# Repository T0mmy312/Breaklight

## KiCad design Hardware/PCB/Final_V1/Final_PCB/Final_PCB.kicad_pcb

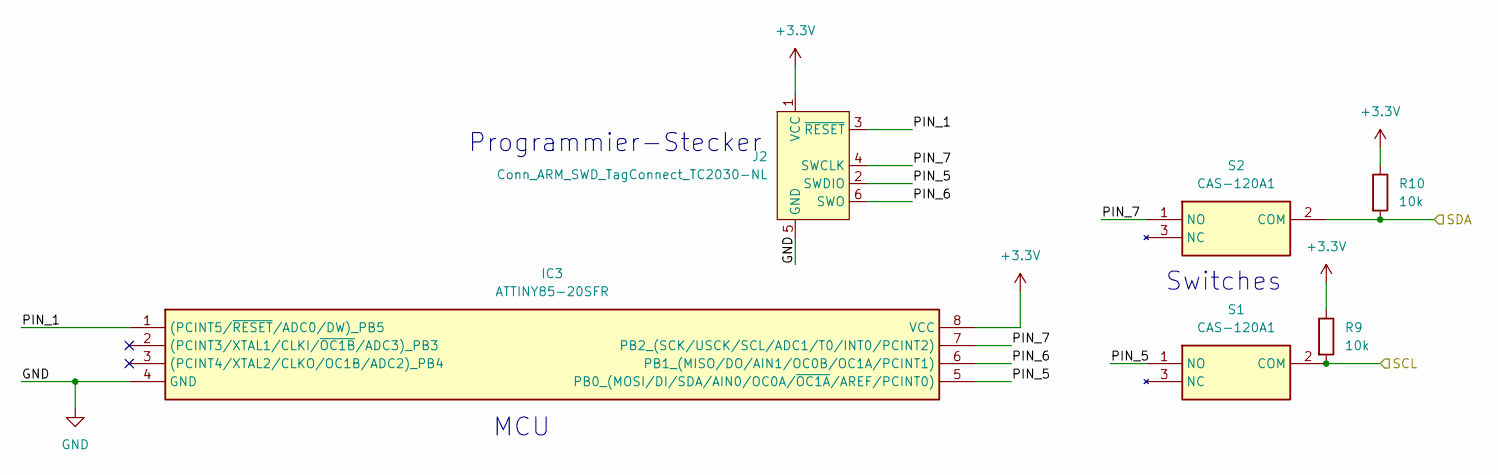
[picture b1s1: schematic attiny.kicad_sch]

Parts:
IC3: ATTINY85-20SFR; SOIC127P798X216-8N; Mouser Part Number 556-ATTINY85-20SFR
J2: Conn_ARM_SWD_TagConnect_TC2030-NL; Tag-Connect_TC2030-IDC-NL_2x03_P1.27mm_Vertical
R9, R10: 10k; R_0603_1608Metric
S1, S2: CAS-120A1; CAS120A1; Mouser Part Number 229-CAS-120A1

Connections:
+3.3V: IC3.8 (VCC), J2.1 (VCC), R9.1, R10.1; also elsewhere on the board
/ATTiny/PIN_1: IC3.1 ((PCINT5/~RESET/ADC0/DW)_PB5), J2.3 (~RESET)
/ATTiny/PIN_5: IC3.5 (PB0_(MOSI/DI/SDA/AIN0/OC0A/~OC1A/AREF/P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), J2.2 (SWDIO), S1.1 (NO)
/ATTiny/PIN_6: IC3.6 (PB1_(MISO/DO/AIN1/OC0B/OC1A/PCINT1)), J2.6 (SWO)
/ATTiny/PIN_7: IC3.7 (PB2_(SCK/USCK/SCL/ADC1/T0/INT0/PCINT2)), J2.4 (SWCLK), S2.1 (NO)
/ATTiny/SCL: R9.2, S1.2 (COM); also elsewhere on the board
/ATTiny/SDA: R10.2, S2.2 (COM); also elsewhere on the board
GND: IC3.4 (GND), J2.5 (GND); also elsewhere on the board

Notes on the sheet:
Switches
Programmier-Stecker
MCU

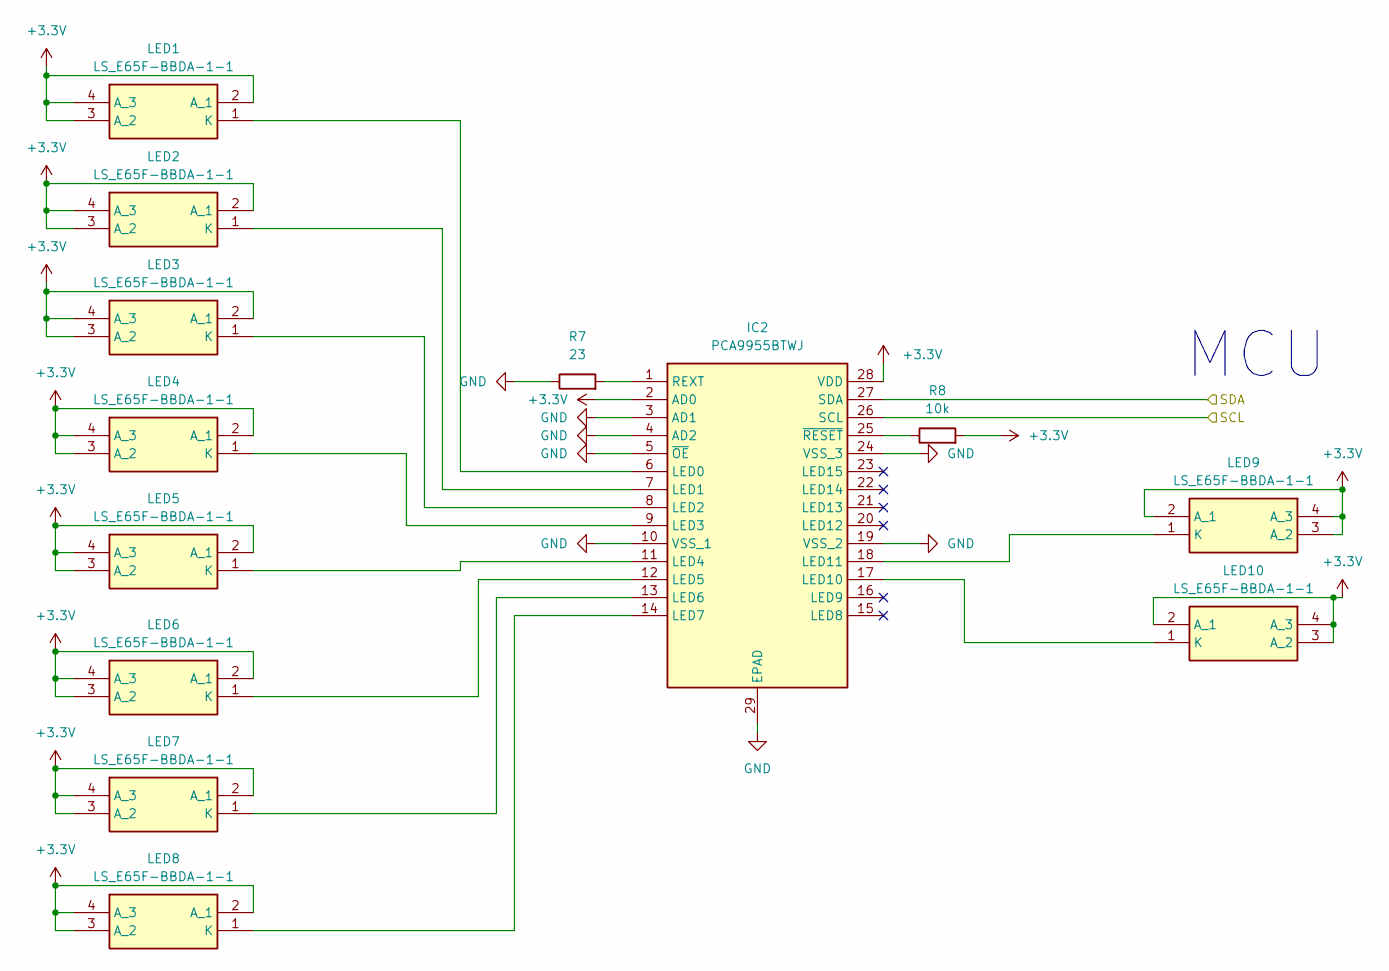
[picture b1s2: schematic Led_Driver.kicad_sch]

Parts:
IC2: PCA9955BTWJ; SOP65P640X110-29N; Manufacturer_Part_Number PCA9955BTWJ
LED1, LED2, LED3, LED4, LED5, LED6, LED7, LED8, LED9, LED10: LS_E65F-BBDA-1-1; LSE65FBBDA11; Mouser Part Number 720-LSE65F-BBDA-1-Z
R7: 23; R_0603_1608Metric
R8: 10k; R_0603_1608Metric

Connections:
+3.3V: IC2.2 (AD0), IC2.28 (VDD), LED1.2 (A_1), LED1.3 (A_2), LED1.4 (A_3), LED2.2 (A_1), LED2.3 (A_2), LED2.4 (A_3), LED3.2 (A_1), LED3.3 (A_2), LED3.4 (A_3), LED4.2 (A_1), LED4.3 (A_2), LED4.4 (A_3), LED5.2 (A_1), LED5.3 (A_2), LED5.4 (A_3), LED6.2 (A_1), LED6.3 (A_2), LED6.4 (A_3), LED7.2 (A_1), LED7.3 (A_2), LED7.4 (A_3), LED8.2 (A_1), LED8.3 (A_2), LED8.4 (A_3), LED9.2 (A_1), LED9.3 (A_2), LED9.4 (A_3), LED10.2 (A_1), LED10.3 (A_2), LED10.4 (A_3), R8.2; also elsewhere on the board
/ATTiny/SCL: IC2.26 (SCL); also elsewhere on the board
/ATTiny/SDA: IC2.27 (SDA); also elsewhere on the board
GND: IC2.3 (AD1), IC2.4 (AD2), IC2.5 (~OE), IC2.10 (VSS_1), IC2.19 (VSS_2), IC2.24 (VSS_3), IC2.29 (EPAD), R7.1; also elsewhere on the board
unnamed: IC2.6 (LED0), LED1.1 (K)
unnamed: IC2.7 (LED1), LED2.1 (K)
unnamed: IC2.8 (LED2), LED3.1 (K)
unnamed: IC2.9 (LED3), LED4.1 (K)
unnamed: IC2.11 (LED4), LED5.1 (K)
unnamed: IC2.12 (LED5), LED6.1 (K)
unnamed: IC2.13 (LED6), LED7.1 (K)
unnamed: IC2.14 (LED7), LED8.1 (K)
unnamed: IC2.17 (LED10), LED10.1 (K)
unnamed: IC2.18 (LED11), LED9.1 (K)
unnamed: IC2.1 (REXT), R7.2
unnamed: IC2.25 (~RESET), R8.1

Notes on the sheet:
MCU

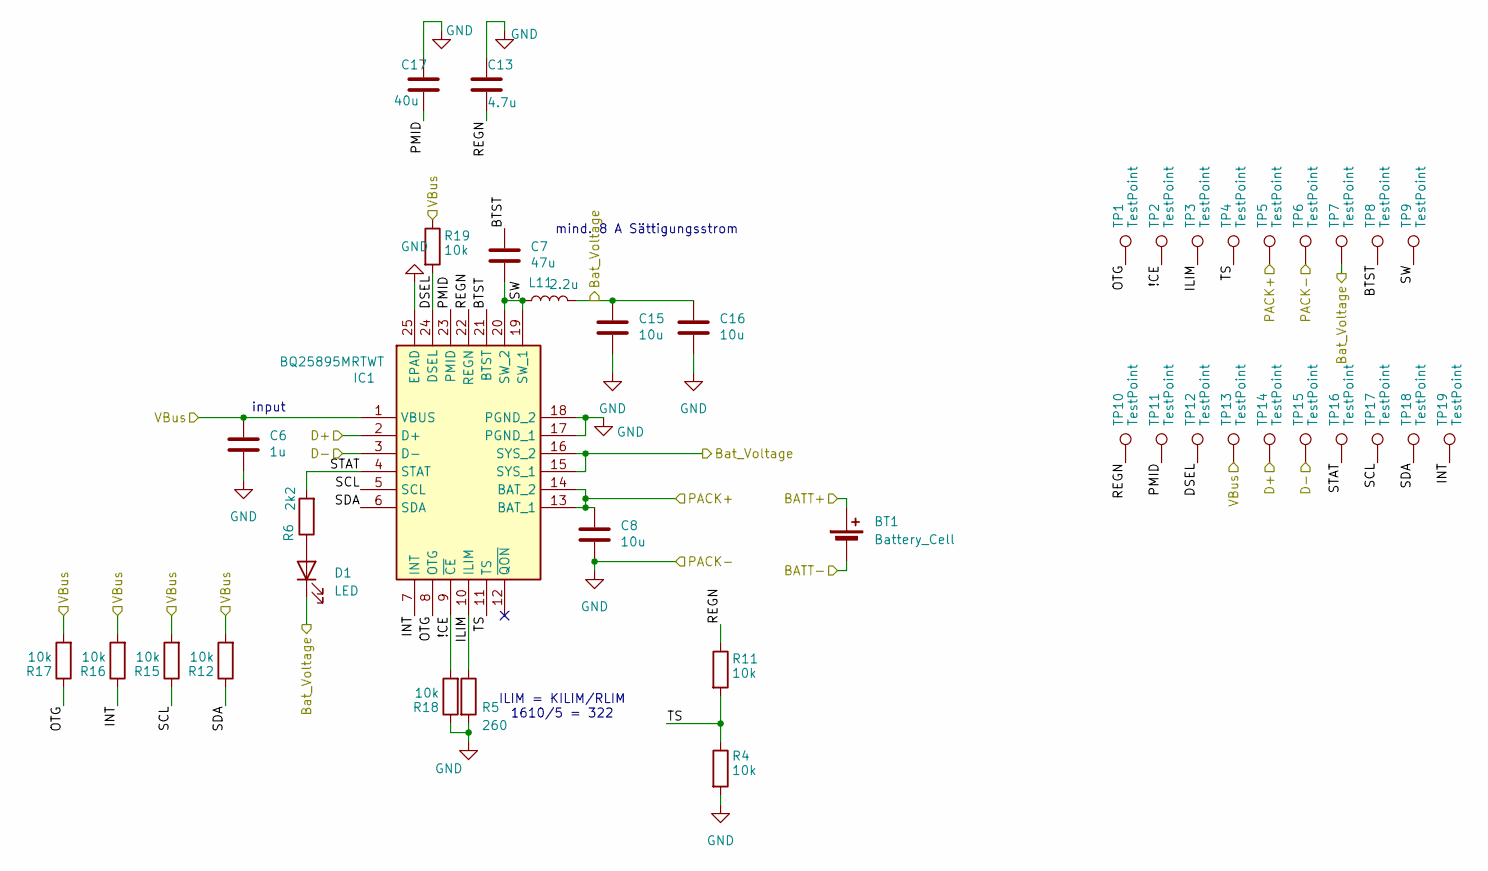
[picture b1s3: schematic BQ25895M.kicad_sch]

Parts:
BT1: Battery_Cell; PinHeader_1x02_P2.54mm_Vertical
C6: 1u; C_0603_1608Metric
C7: 47u; C_0603_1608Metric
C8, C15, C16: 10u; C_0603_1608Metric
C13: 4.7u; C_0603_1608Metric
C17: 40u; C_0603_1608Metric
D1: LED; LED_0603_1608Metric
IC1: BQ25895MRTWT; QFN50P400X400X80-25N-D; Mouser Part Number 595-BQ25895MRTWT
L11: 2.2u; L_0603_1608Metric
R4, R11, R12, R15, R16, R17, R18, R19: 10k; R_0603_1608Metric
R5: 260; R_0603_1608Metric
R6: 2k2; R_0603_1608Metric
TP1, TP2, TP3, TP4, TP5, TP6, TP7, TP8, TP9, TP10, TP11, TP12, TP13, TP14, TP15, TP16, TP17, TP18, TP19: TestPoint; TestPoint_Pad_1.5x1.5mm

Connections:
/BMS/BATT+: BT1.1 (+); also elsewhere on the board
/BMS/PACK+: C8.1, IC1.13 (BAT_1), IC1.14 (BAT_2), TP5.1; also elsewhere on the board
/BQ25895M/!CE: IC1.9 (~CE), R18.2, TP2.1
/BQ25895M/BTST: C7.1, IC1.21 (BTST), TP8.1
/BQ25895M/Bat_Voltage: C15.1, C16.1, D1.1 (K), IC1.15 (SYS_1), IC1.16 (SYS_2), L11.2, TP7.1; also elsewhere on the board
/BQ25895M/D+: IC1.2 (D+), TP14.1; also elsewhere on the board
/BQ25895M/D-: IC1.3 (D-), TP15.1; also elsewhere on the board
/BQ25895M/DSEL: IC1.24 (DSEL), R19.2, TP12.1
/BQ25895M/ILIM: IC1.10 (ILIM), R5.1, TP3.1
/BQ25895M/INT: IC1.7 (INT), R16.1, TP19.1
/BQ25895M/OTG: IC1.8 (OTG), R17.1, TP1.1
/BQ25895M/PMID: C17.2, IC1.23 (PMID), TP11.1
/BQ25895M/REGN: C13.2, IC1.22 (REGN), R11.1, TP10.1
/BQ25895M/SCL: IC1.5 (SCL), R15.1, TP17.1
/BQ25895M/SDA: IC1.6 (SDA), R12.1, TP18.1
/BQ25895M/STAT: IC1.4 (STAT), R6.2, TP16.1
/BQ25895M/SW: C7.2, IC1.19 (SW_1), IC1.20 (SW_2), L11.1, TP9.1
/BQ25895M/TS: IC1.11 (TS), R4.1, R11.2, TP4.1
/BQ25895M/VBus: C6.1, IC1.1 (VBUS), R12.2, R15.2, R16.2, R17.2, R19.1, TP13.1; also elsewhere on the board
GND: BT1.2 (-), C6.2, C8.2, C13.1, C15.2, C16.2, C17.1, IC1.17 (PGND_1), IC1.18 (PGND_2), IC1.25 (EPAD), R4.2, R5.2, R18.1, TP6.1; also elsewhere on the board
unnamed: D1.2 (A), R6.1

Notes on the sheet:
ILIM = KILIM/RLIM 1610/5 = 322
mind. 8 A Sättigungsstrom
input

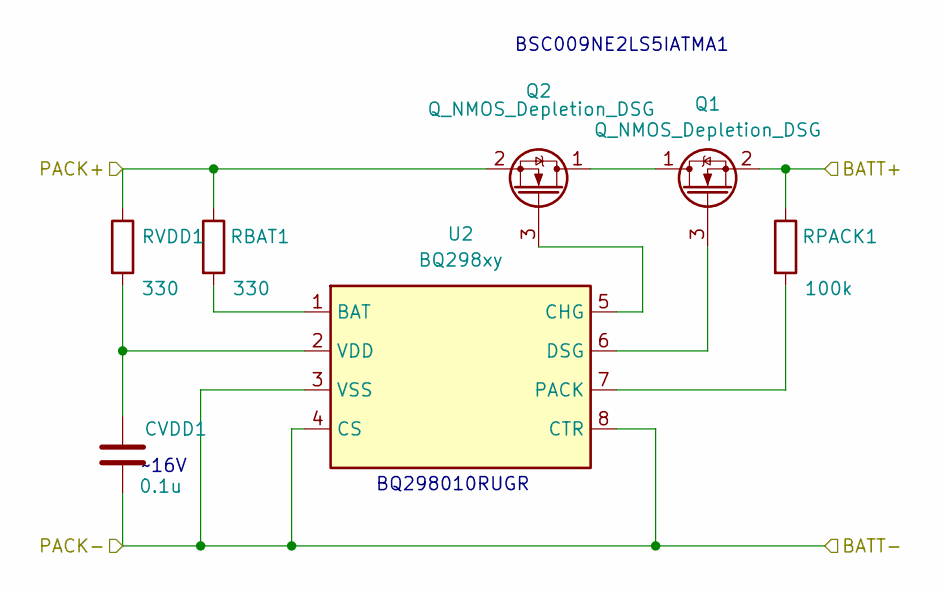
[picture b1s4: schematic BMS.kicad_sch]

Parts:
CVDD1: 0.1u; C_0603_1608Metric_Pad1.08x0.95mm_HandSolder
Q1, Q2: Q_NMOS_Depletion_DSG; MOSFET_BSC093N04LSGATMA1
RBAT1: 330; R_0603_1608Metric
RPACK1: 100k; R_0603_1608Metric
RVDD1: 330; R_0603_1608Metric
U2: BQ298xy; QFN50P150X150X40-8N

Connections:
/BMS/BATT+: Q1.2 (S), RPACK1.1; also elsewhere on the board
/BMS/PACK+: Q2.2 (S), RBAT1.1, RVDD1.1; also elsewhere on the board
GND: CVDD1.2, U2.3 (VSS), U2.4 (CS), U2.8 (CTR); also elsewhere on the board
unnamed: Q1.1 (D), Q2.1 (D)
unnamed: Q1.3 (G), U2.6 (DSG)
unnamed: Q2.3 (G), U2.5 (CHG)
unnamed: RBAT1.2, U2.1 (BAT)
unnamed: RPACK1.2, U2.7 (PACK)
unnamed: CVDD1.1, RVDD1.2, U2.2 (VDD)

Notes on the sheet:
BSC009NE2LS5IATMA1
~16V
BQ298010RUGR

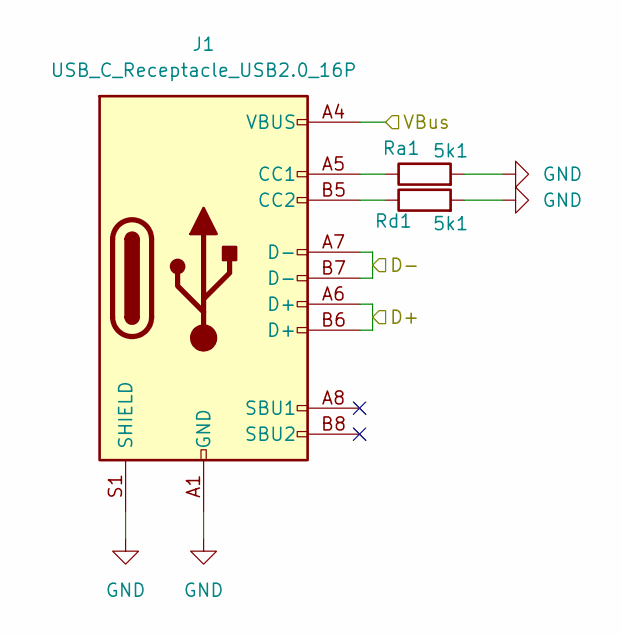
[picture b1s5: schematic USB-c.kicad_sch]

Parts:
J1: USB_C_Receptacle_USB2.0_16P; USB_C_Receptacle_GCT_USB4085
Ra1: 5k1; R_0603_1608Metric
Rd1: 5k1; R_0603_1608Metric

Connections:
/BQ25895M/D+: J1.A6 (D+), J1.B6 (D+); also elsewhere on the board
/BQ25895M/D-: J1.A7 (D-), J1.B7 (D-); also elsewhere on the board
/BQ25895M/VBus: J1.A4 (VBUS), J1.A9 (VBUS), J1.B4 (VBUS), J1.B9 (VBUS); also elsewhere on the board
GND: J1.A1 (GND), J1.A12 (GND), J1.B1 (GND), J1.B12 (GND), J1.S1 (SHIELD), Ra1.2, Rd1.2; also elsewhere on the board
unnamed: J1.A5 (CC1), Ra1.1
unnamed: J1.B5 (CC2), Rd1.1

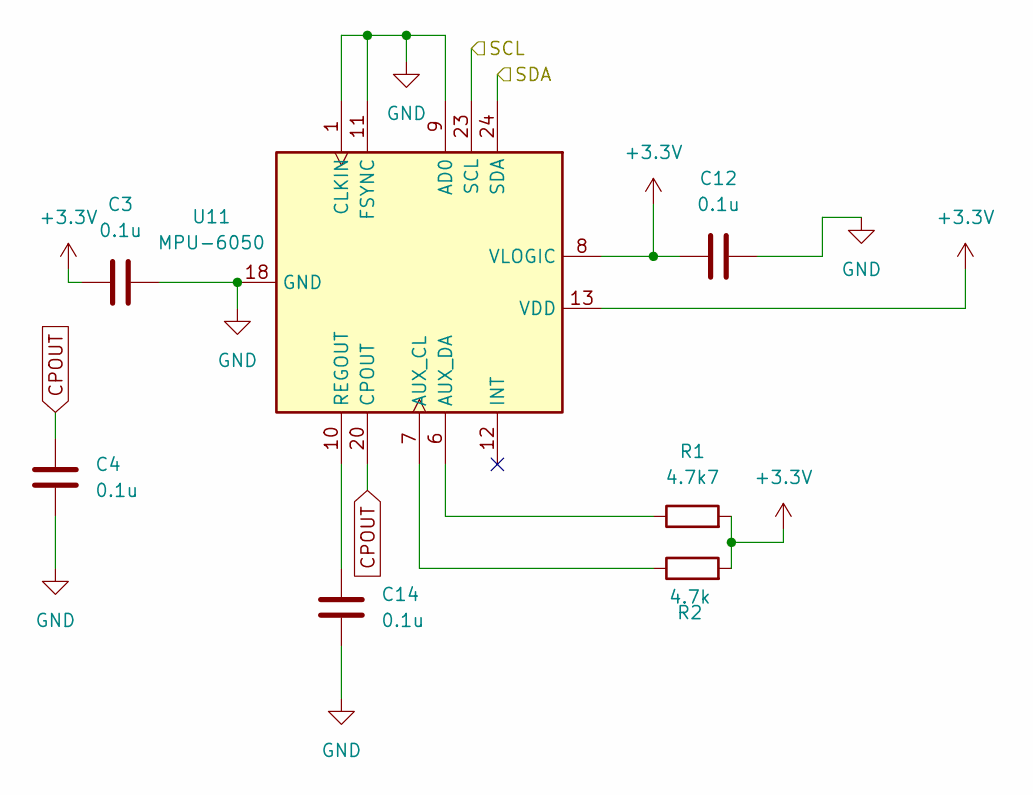
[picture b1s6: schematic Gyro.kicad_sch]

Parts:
C3, C4, C12, C14: 0.1u; C_0603_1608Metric_Pad1.08x0.95mm_HandSolder
R1: 4.7k7; R_0603_1608Metric
R2: 4.7k; R_0603_1608Metric
U11: MPU-6050; InvenSense_QFN-24_4x4mm_P0.5mm

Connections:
+3.3V: C3.1, C12.1, R1.2, R2.2, U11.8 (VLOGIC), U11.13 (VDD); also elsewhere on the board
/ATTiny/SCL: U11.23 (SCL); also elsewhere on the board
/ATTiny/SDA: U11.24 (SDA); also elsewhere on the board
CPOUT: C4.2, U11.20 (CPOUT)
GND: C3.2, C4.1, C12.2, C14.2, U11.1 (CLKIN), U11.9 (AD0), U11.11 (FSYNC), U11.18 (GND); also elsewhere on the board
unnamed: R2.1, U11.7 (AUX_CL)
unnamed: R1.1, U11.6 (AUX_DA)
unnamed: C14.1, U11.10 (REGOUT)

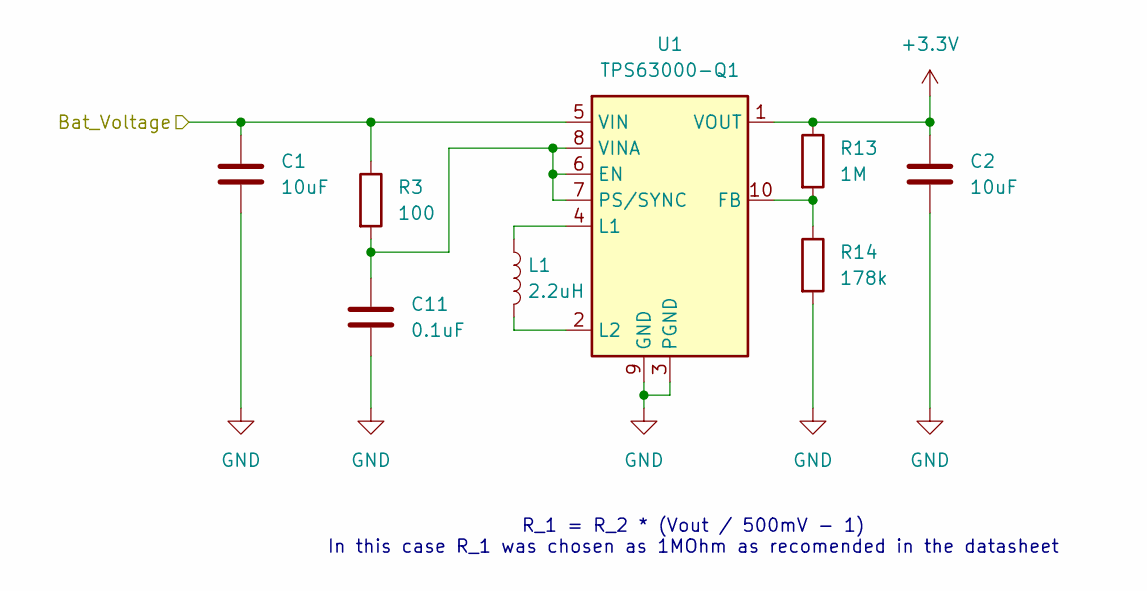
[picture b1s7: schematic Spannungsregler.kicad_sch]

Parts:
C1, C2: 10uF; C_0603_1608Metric
C11: 0.1uF; C_0603_1608Metric
L1: 2.2uH; L_0805_2012Metric
R3: 100; R_0603_1608Metric
R13: 1M; R_0603_1608Metric
R14: 178k; R_0603_1608Metric
U1: TPS63000-Q1; Texas_DRC0010J_ThermalVias

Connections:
+3.3V: C2.1, R13.1, U1.1 (VOUT); also elsewhere on the board
/BQ25895M/Bat_Voltage: C1.1, R3.1, U1.5 (VIN); also elsewhere on the board
GND: C1.2, C2.2, C11.2, R14.2, U1.3 (PGND), U1.9 (GND), U1.11 (PGND); also elsewhere on the board
unnamed: C11.1, R3.2, U1.6 (EN), U1.7 (PS/SYNC), U1.8 (VINA)
unnamed: R13.2, R14.1, U1.10 (FB)
unnamed: L1.1, U1.4 (L1)
unnamed: L1.2, U1.2 (L2)

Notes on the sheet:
R_1 = R_2 * (Vout / 500mV - 1) In this case R_1 was chosen as 1MOhm as recomended in the datasheet

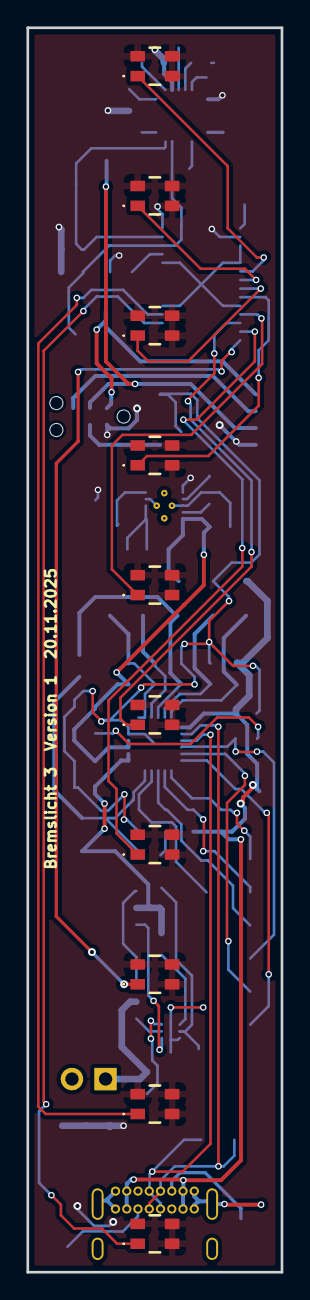
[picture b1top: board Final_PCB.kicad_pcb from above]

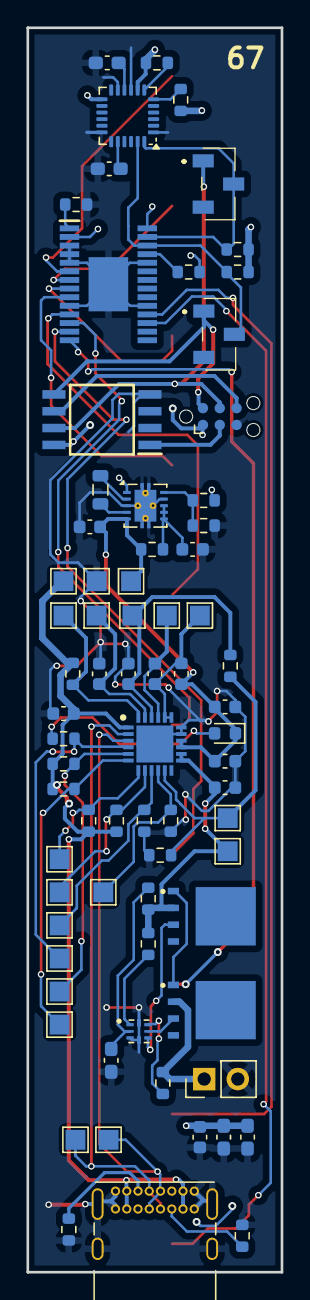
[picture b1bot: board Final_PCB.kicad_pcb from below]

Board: 2 copper layers, 19.2 x 94.0 mm, 84 parts (74 on the bottom side), 56 nets.

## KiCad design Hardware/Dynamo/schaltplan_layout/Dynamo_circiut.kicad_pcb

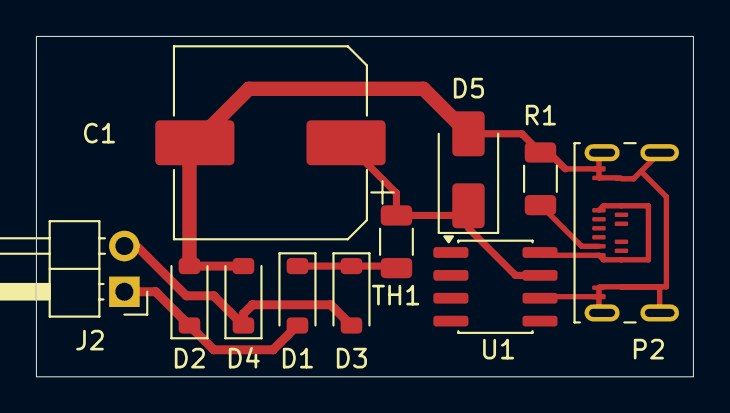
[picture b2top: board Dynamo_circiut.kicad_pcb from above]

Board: 2 copper layers, 36.5 x 18.9 mm, 11 parts (0 on the bottom side), 7 nets.

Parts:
C1: 470µ; CP_Elec_10x10.5
D1, D2, D3, D4: 1N5819; D_SOD-123
D5: SMAJ30A; D_SMA
J2: Conn_01x02_Socket; PinHeader_1x02_P2.54mm_Horizontal
P2: USB_C_Plug_USB2.0; USB_C_Receptacle_Amphenol_124019772112A
R1: 5.1k; R_1206_3216Metric
TH1: Littelfuse 1206L050WR; R_1206_3216Metric
U1: LM2594HVM-5.0; SOIC-8_3.9x4.9mm_P1.27mm

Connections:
/Dynamo: D3.2 (A), D4.1 (K), J2.2
/Dynamo_minus: D1.2 (A), D2.1 (K), J2.1
unnamed: D1.1 (K), D3.1 (K), TH1.2
unnamed: C1.2, D2.2 (A), D4.2 (A), D5.2 (A2), P2.A1 (GND), P2.A12 (GND), P2.B1 (GND), P2.B12 (GND), P2.S1 (SHIELD), R1.2, U1.6 (GND)
unnamed: C1.1, D5.1 (A1), TH1.1, U1.7 (VIN)
unnamed: P2.A5 (CC), R1.1
unnamed: P2.A4 (VBUS), P2.A9 (VBUS), P2.B4 (VBUS), P2.B9 (VBUS), U1.8 (OUT)

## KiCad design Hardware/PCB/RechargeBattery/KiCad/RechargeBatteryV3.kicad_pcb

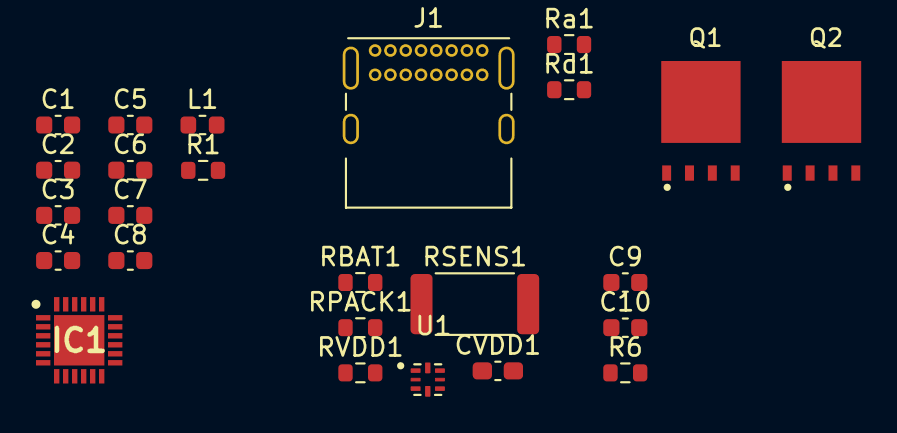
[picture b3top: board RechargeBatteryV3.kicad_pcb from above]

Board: 2 copper layers, 25 parts (0 on the bottom side), 22 nets, no tracks yet.

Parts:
C1, C10: 1u; C_0603_1608Metric
C2, C9: 22u; C_0603_1608Metric
C3, C5, C6: 10u; C_0603_1608Metric
C4, C7: 4.7u; C_0603_1608Metric
C8: 40u; C_0603_1608Metric
CVDD1: 0.1u; C_0603_1608Metric_Pad1.08x0.95mm_HandSolder
IC1: BQ25895MRTWT; QFN50P400X400X80-25N-D
J1: USB_C_Receptacle_USB2.0_16P; USB_C_Receptacle_GCT_USB4085
L1: 2.2u; L_0603_1608Metric
Q1, Q2: Q_NMOS_Depletion_DSG; MOSFET_BSC093N04LSGATMA1
R1: 322; R_0603_1608Metric
R6: 2k2; R_0603_1608Metric
RBAT1: 330; R_0603_1608Metric
RPACK1: 100k; R_0603_1608Metric
RSENS1: 322; R_2512_6332Metric
RVDD1: 330; R_0603_1608Metric
Ra1: 5k1; R_0603_1608Metric
Rd1: 5k1; R_0603_1608Metric
U1: BQ298xy; QFN50P150X150X40-8N

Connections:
/BMS/BATT+: Q1.2 (S), RPACK1.1
/BMS/BATT-: RSENS1.2, U1.4 (CS), U1.8 (CTR)
/BMS/PACK+: C3.1, IC1.13 (BAT_1), IC1.14 (BAT_2), Q2.2 (S), RBAT1.1, RVDD1.1
/BQ25895M/BTST: C4.1, IC1.21 (BTST)
/BQ25895M/D+: IC1.2 (D+), J1.A6 (D+), J1.B6 (D+)
/BQ25895M/D-: IC1.3 (D-), J1.A7 (D-), J1.B7 (D-)
/BQ25895M/Output: C5.1, C6.1, IC1.15 (SYS_1), IC1.16 (SYS_2), L1.2
/BQ25895M/PMID: C8.2, IC1.23 (PMID)
/BQ25895M/REGN: C7.2, C10.2, IC1.22 (REGN)
/BQ25895M/TS: C1.1, C2.1, C9.1, IC1.1 (VBUS), IC1.11 (TS), J1.A4 (VBUS), J1.A9 (VBUS), J1.B4 (VBUS), J1.B9 (VBUS)
GND: C1.2, C2.2, C3.2, C5.2, C6.2, C7.1, C8.1, C9.2, C10.1, CVDD1.2, IC1.9 (~CE), IC1.12 (~QON), IC1.17 (PGND_1), IC1.18 (PGND_2), IC1.24 (DSEL), IC1.25 (EPAD), J1.A1 (GND), J1.A12 (GND), J1.B1 (GND), J1.B12 (GND), J1.S1 (SHIELD), R1.2, RSENS1.1, Ra1.2, Rd1.2, U1.3 (VSS)
unnamed: IC1.10 (ILIM), R1.1
unnamed: IC1.4 (STAT), R6.2
unnamed: C4.2, IC1.19 (SW_1), IC1.20 (SW_2), L1.1
unnamed: J1.A5 (CC1), Ra1.1
unnamed: J1.B5 (CC2), Rd1.1
unnamed: Q1.1 (D), Q2.1 (D)
unnamed: Q1.3 (G), U1.6 (DSG)
unnamed: Q2.3 (G), U1.5 (CHG)
unnamed: RBAT1.2, U1.1 (BAT)
unnamed: RPACK1.2, U1.7 (PACK)
unnamed: CVDD1.1, RVDD1.2, U1.2 (VDD)

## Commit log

2025-09-15 initial File Structure
2025-09-15 added Rules and Research directories
2025-09-22 added tutorial
2025-09-22 test
2025-09-22 initial research for SMD-LEDs
2025-09-22 Add Samsung INR21700-50S datasheet and selection rationale
2025-09-22 created Doc.md and research folder
2025-09-22 added another LED option doc
2025-09-22 format update docs for LED
2025-09-22 made a charcing circut. that works with our usb-c connctor and our battery
2025-09-22 changed batterie to Battery
2025-09-22 added mcu research and led driver ic in the docs
2025-09-22 gyro research
2025-09-22 added ATTiny Test project
2025-09-22 Research Gyro
2025-09-22 added base case design and technical drawing
2025-09-29 added PCB-outline
2025-09-29 added mcu documentation reguarding programming
2025-10-06 Recharge Batterie V1
2025-10-06 Create GYRO_Shematic
2025-10-06 Recharge Batterie V2
2025-10-06 GYRO_Shematic
2025-10-06 Dynamo_Research
2025-10-06 Dynamo Research
2025-10-06 Dynamo_Circiut
2025-10-14 added a doc.md for the charcing port where I descriped why we picked it
2025-10-14 batterie recharing system V3 with BQ25895M chip
2025-10-14 minor refactoring
2025-10-20 rechargeBatterie schematic finsished
2025-10-20 added Led_Driver and Documentation
2025-10-20 move Gyro-Folder
2025-10-20 added more code for debug
2025-10-30 finished schematic
2025-11-03 fixed Schematics
2025-11-03 added Voltage regulator to get constant 3.3V Voltage and fixed some issues
2025-11-03 fixed last commit, because it was wrong
2025-11-03 fixing xhematics
2025-11-10 fixed curcuit, mainly the charge curcuit
2025-11-16 #1: Add footprints to the components
2025-11-17 added footprints for BQ298010RUGR and BSC009NE2LS5IATMA1
2025-11-17 #2: fix 2 footprints
2025-11-17 started layouting
2025-11-17 #3: fix-1-footprint
2025-11-17 reapplied fixes because of commiting problems
2025-11-17 fixed some minor mistakes and added test pads for the battery charger
2025-11-17 updated git tutorial
2025-11-17 layout_schaltplan_added
2025-11-17 #4: Layout-Session-17-11-25
2025-11-22 #5: finish layout
2025-11-23 made a few pcb tweaks
2025-11-23 Devre kartının çalışmasını ummalıyız
2025-11-23 a few pcb edits
2025-11-24 add pcb fixes
2025-12-01 added project structure
2026-02-02 add ATTiny85 code
